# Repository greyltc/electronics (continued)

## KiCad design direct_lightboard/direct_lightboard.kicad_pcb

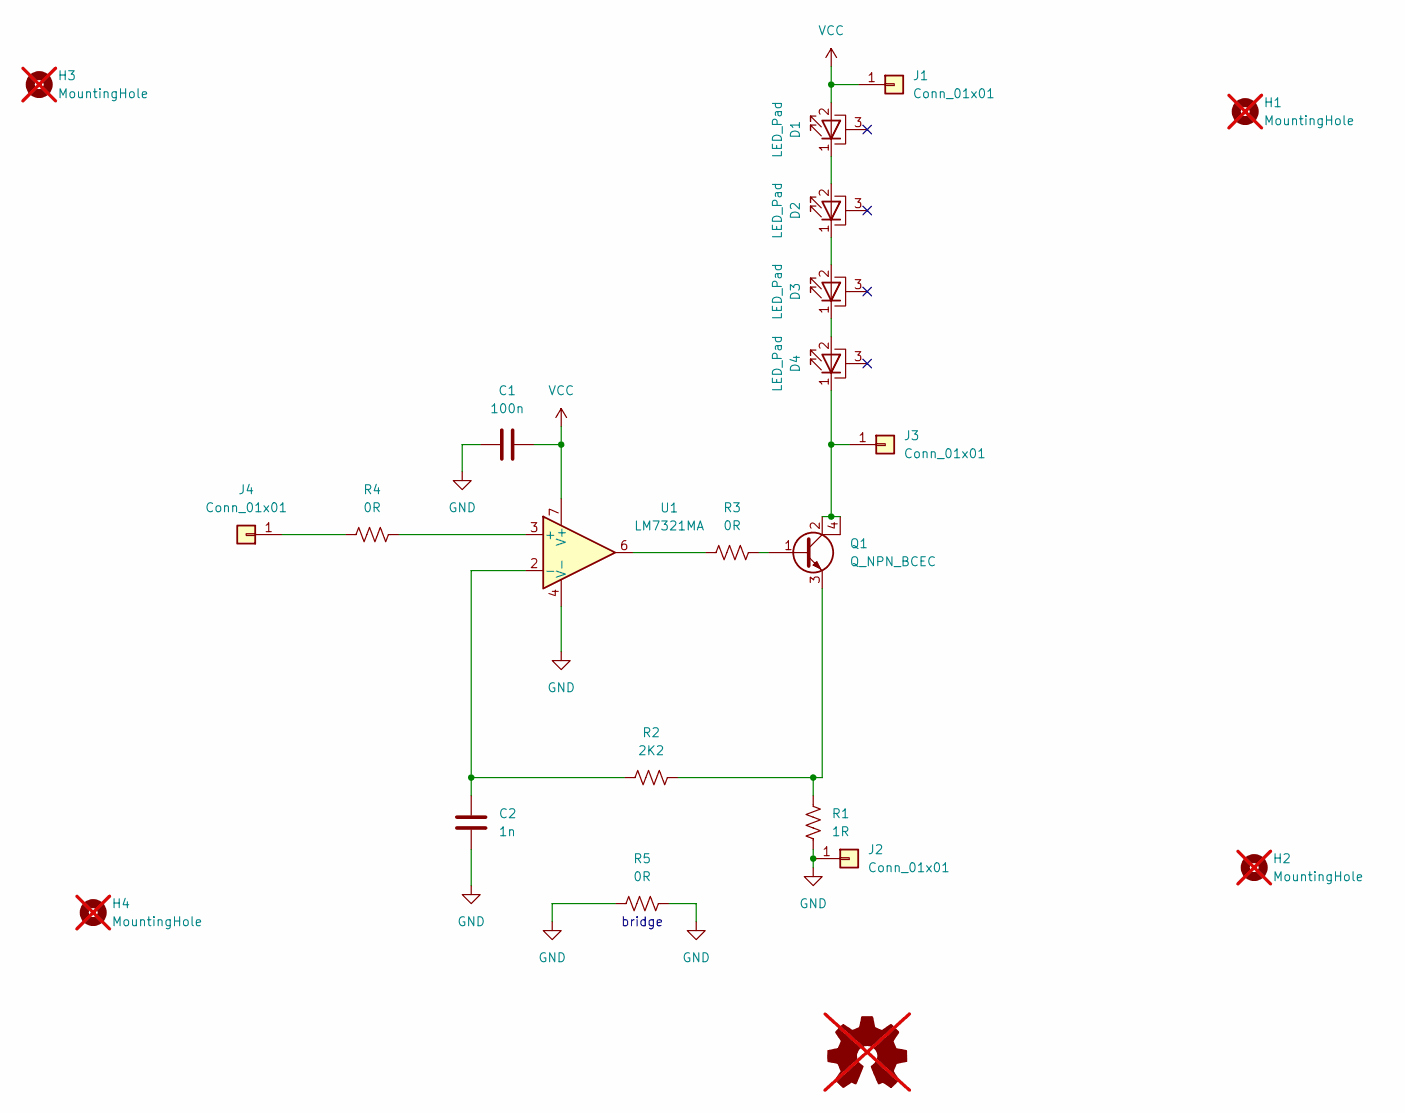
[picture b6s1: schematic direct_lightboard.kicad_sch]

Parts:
C1: 100n; C_0805_2012Metric_Pad1.18x1.45mm_HandSolder; LCSC C77082
C2: 1n; C_0805_2012Metric_Pad1.18x1.45mm_HandSolder; LCSC C46653
D1, D2, D3, D4: LED_Pad; LED_3x3_DIRECT_CU; LCSC C2899049
H1, H2, H3, H4: MountingHole; MountingHole_4mm; not fitted
J1, J2, J3, J4: Conn_01x01; TE_2834006-1_1x01_P4.0mm_Horizontal; LCSC C306142
Q1: Q_NPN_BCEC; SOT-223; LCSC C24098
R1: 1R; R_2512_6332Metric_Pad1.40x3.35mm_HandSolder; LCSC C2941595
R2: 2K2; R_0805_2012Metric_Pad1.20x1.40mm_HandSolder; LCSC C3008897
R3, R4: 0R; R_0805_2012Metric_Pad1.20x1.40mm_HandSolder; LCSC C844192
R5: 0R; R_1206_3216Metric_Pad1.30x1.75mm_HandSolder; LCSC C844862
SYM1: Logo_Open_Hardware_Small; site_small; not fitted
U1: LM7321MA; VSSOP-8_3.0x3.0mm_P0.65mm; LCSC C81665

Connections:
GND: C1.1, C2.1, J2.1, R1.2, R5.1, R5.2, U1.4 (V-)
unnamed: D1.1 (K), D2.2 (A)
unnamed: D2.1 (K), D3.2 (A)
unnamed: D3.1 (K), D4.2 (A)
unnamed: D4.1 (K), J3.1, Q1.2 (C), Q1.4 (C)
unnamed: J4.1, R4.1
unnamed: Q1.1 (B), R3.2
unnamed: Q1.3 (E), R1.1, R2.2
unnamed: R3.1, U1.6
unnamed: R4.2, U1.3 (+)
unnamed: C2.2, R2.1, U1.2 (-)
VCC: C1.2, D1.2 (A), J1.1, U1.7 (V+)

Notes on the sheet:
bridge

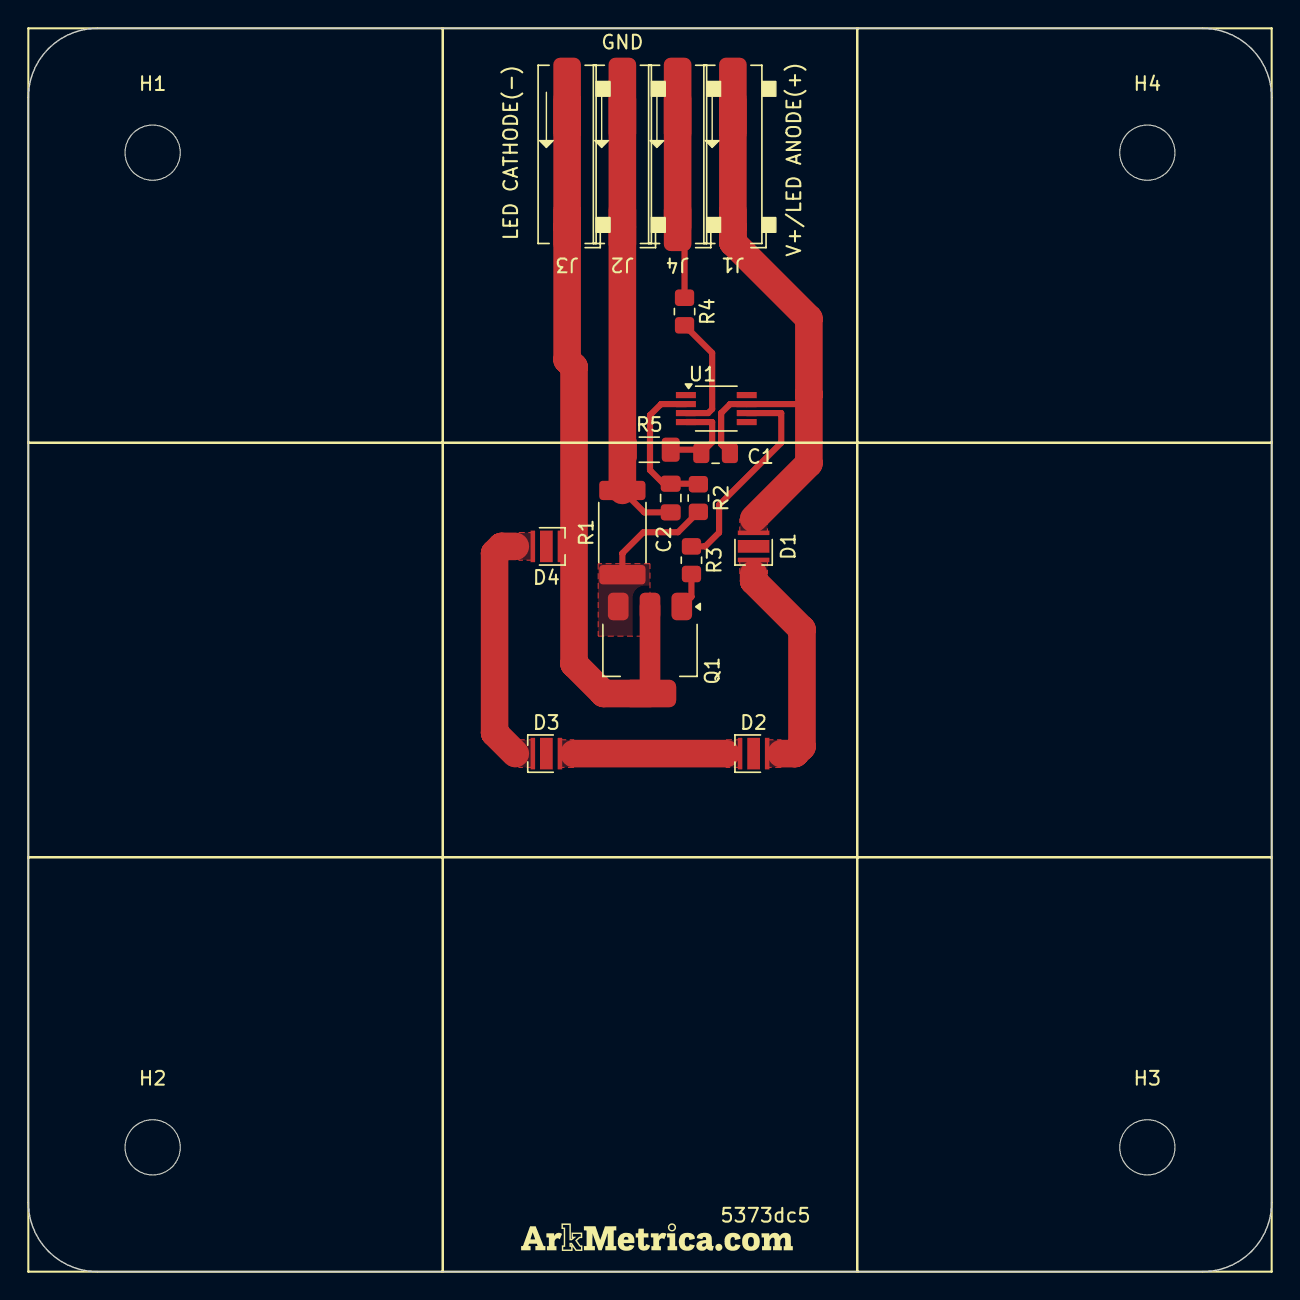
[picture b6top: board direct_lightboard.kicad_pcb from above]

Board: 2 copper layers, 90.0 x 90.0 mm, 22 parts (0 on the bottom side), 12 nets.

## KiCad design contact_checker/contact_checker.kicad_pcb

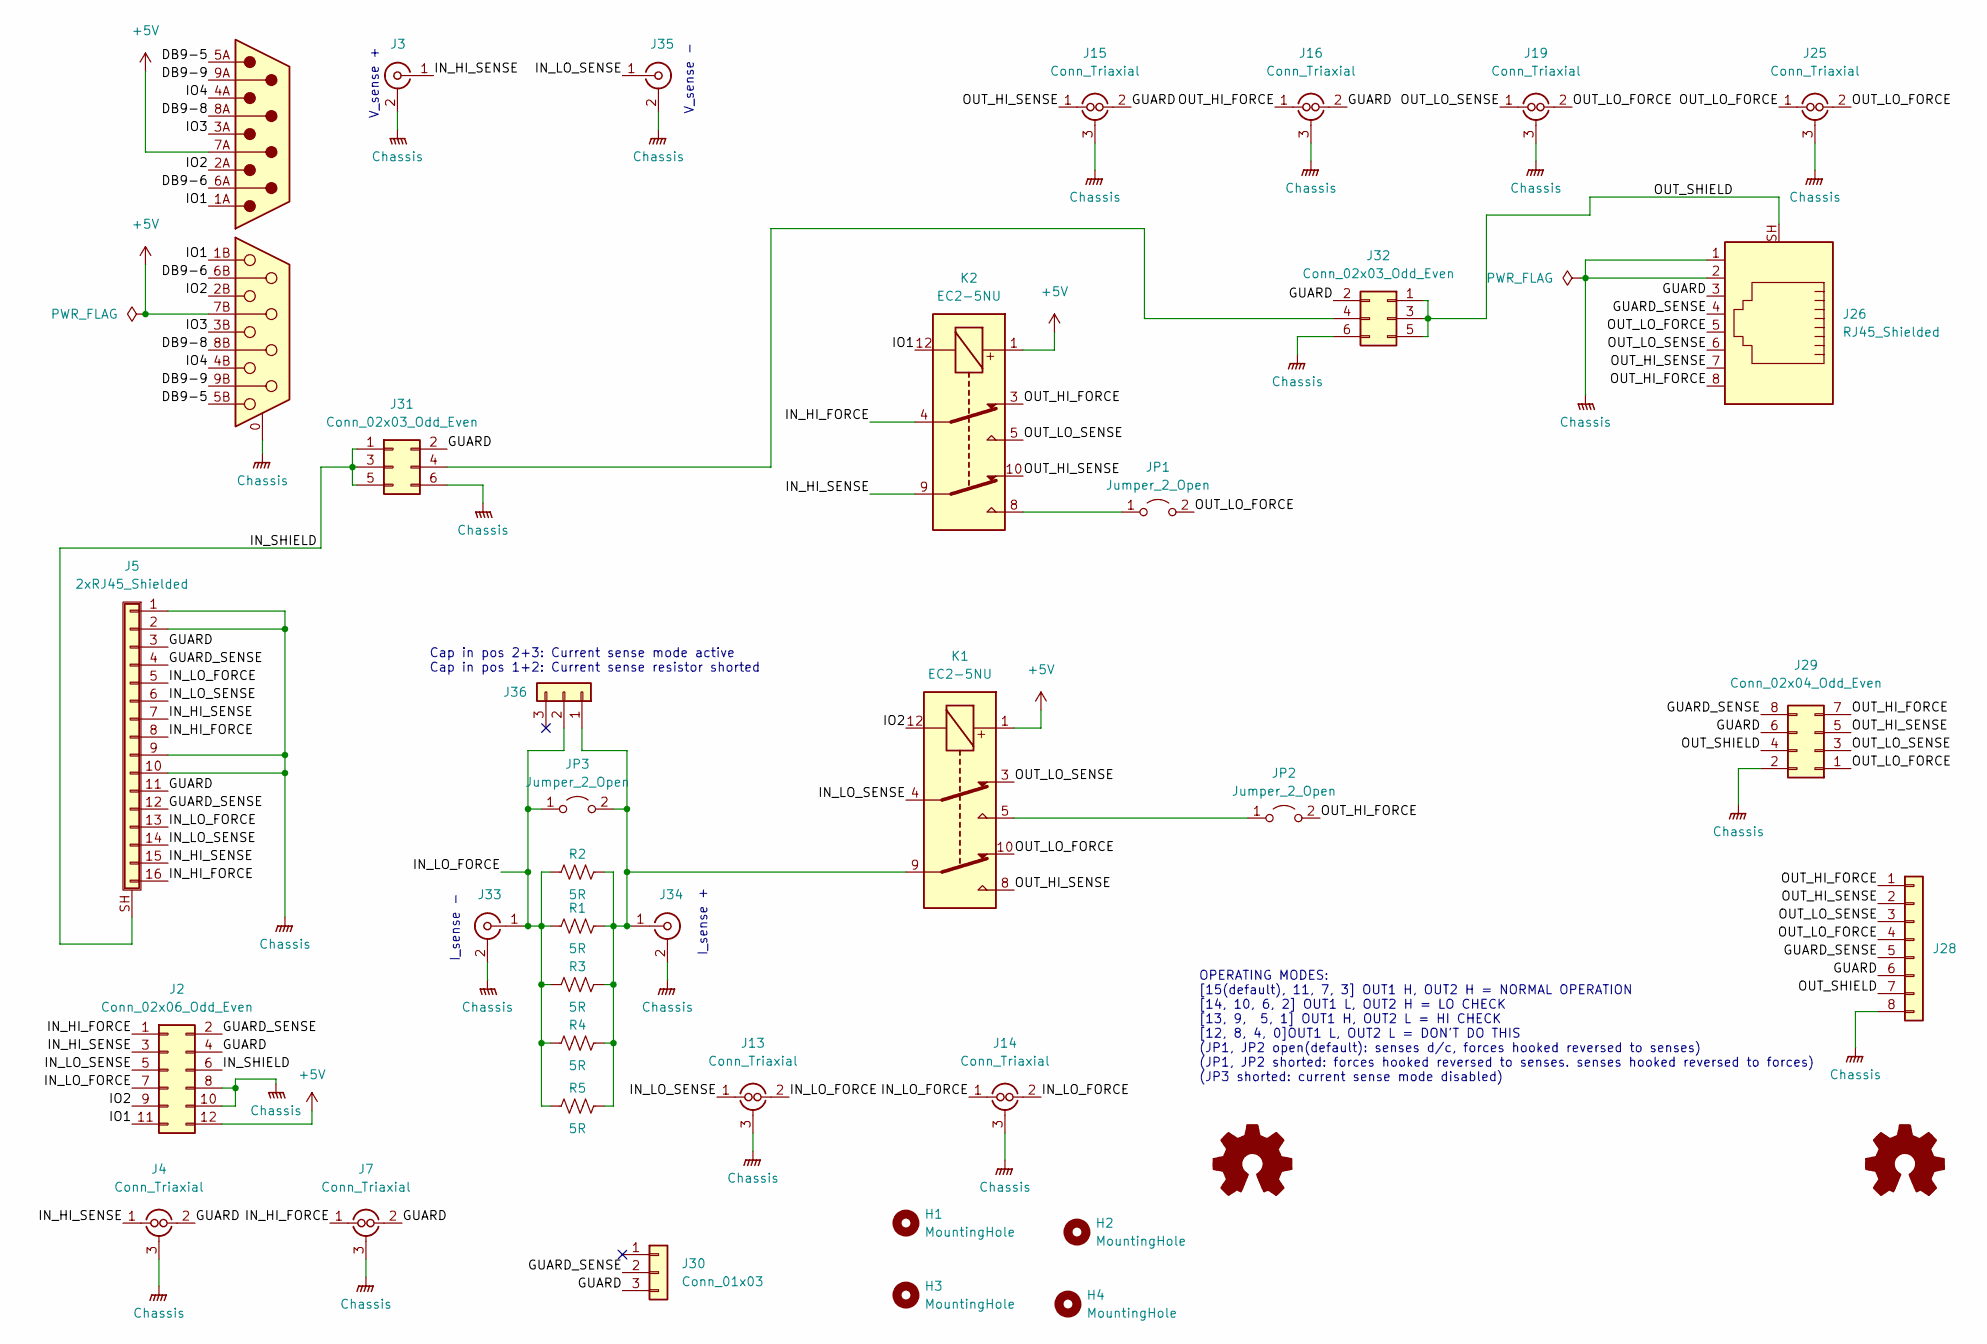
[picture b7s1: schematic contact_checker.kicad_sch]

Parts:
H1, H2, H3, H4: MountingHole; MountingHole_3.2mm_M3_ISO7380
J1: DB9_Male_Female_Stack_MountingHoles; DSUB-9_Male_Female_Vertical_Stack_P2.77x2.84mm_MountingHoles
J2: Conn_02x06_Odd_Even; IDC-Header_2x06_P2.54mm_Horizontal
J3, J33, J34, J35: Conn_Coaxial; U.FL_Molex_MCRF_73412-0110_Vertical
J4, J7, J13, J14, J15, J16, J19, J25: Conn_Triaxial; PinHeader_1x03_P2.54mm_Vertical
J5: 2xRJ45_Shielded; RJ45_WURTH_615016240521
J26: RJ45_Shielded; RJ45_WURTH_61500814221
J28: Conn_01x08; PhoenixContact_MC_1,5_8-GF-3.5_1x08_P3.50mm_Horizontal_Thre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
J29: Conn_02x04_Odd_Even; IDC-Header_2x04_P2.54mm_Horizontal
J30, J36: Conn_01x03; PinHeader_1x03_P2.54mm_Horizontal
J31, J32: Conn_02x03_Odd_Even; PinHeader_2x03_P2.54mm_Vertical
JP1, JP2: Jumper_2_Open; SolderJumper-2_P1.3mm_Open_TrianglePad1.0x1.5mm
JP3: Jumper_2_Open; SolderJumper-2_P1.3mm_Open_RoundedPad1.0x1.5mm
K1, K2: EC2-5NU; Relay_DPDT_Kemet_EC2
LOGO1, LOGO2: Logo_Open_Hardware_Small; logo
R1, R2, R3, R4, R5: 5R; R_2512_6332Metric_Pad1.40x3.35mm_HandSolder

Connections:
+5V: J1.7A, J1.7B, J2.12, K1.1, K2.1
/DB9-5: J1.5A, J1.5B
/DB9-6: J1.6A, J1.6B
/DB9-8: J1.8A, J1.8B
/DB9-9: J1.9A, J1.9B
/GUARD: J2.4, J4.2 (In2), J5.3, J5.11, J7.2 (In2), J15.2 (In2), J16.2 (In2), J26.3, J28.6, J29.6, J30.3, J31.2, J32.2
/GUARD_SENSE: J2.2, J5.4, J5.12, J26.4, J28.5, J29.8, J30.2
/IN_HI_FORCE: J2.1, J5.8, J5.16, J7.1 (In1), K2.4
/IN_HI_SENSE: J2.3, J3.1 (In), J4.1 (In1), J5.7, J5.15, K2.9
/IN_LO_FORCE: J2.7, J5.5, J5.13, J13.2 (In2), J14.1 (In1), J14.2 (In2), J33.1 (In), J36.2, JP3.1 (A), R1.1, R2.1, R3.1, R4.1, R5.1
/IN_LO_SENSE: J2.5, J5.6, J5.14, J13.1 (In1), J35.1 (In), K1.4
/IN_SHIELD: J2.6, J5.SH (Shield), J31.1, J31.3, J31.5
/IO1: J1.1A, J1.1B, J2.11, K2.12
/IO2: J1.2A, J1.2B, J2.9, K1.12
/IO3: J1.3A, J1.3B
/IO4: J1.4A, J1.4B
/OUT_HI_FORCE: J16.1 (In1), J26.8, J28.1, J29.7, JP2.2 (B), K2.3
/OUT_HI_SENSE: J15.1 (In1), J26.7, J28.2, J29.5, K1.8, K2.10
/OUT_LO_FORCE: J19.2 (In2), J25.1 (In1), J25.2 (In2), J26.5, J28.4, J29.1, JP1.2 (B), K1.10
/OUT_LO_SENSE: J19.1 (In1), J26.6, J28.3, J29.3, K1.3, K2.5
/OUT_SHIELD: J26.SH, J28.7, J29.4, J32.1, J32.3, J32.5
GNDPWR: J1.0 (PAD), J2.8, J2.10, J3.2 (Ext), J4.3 (Ext), J5.1, J5.2, J5.9, J5.10, J7.3 (Ext), J13.3 (Ext), J14.3 (Ext), J15.3 (Ext), J16.3 (Ext), J19.3 (Ext), J25.3 (Ext), J26.1, J26.2, J28.8, J29.2, J31.6, J32.6, J33.2 (Ext), J34.2 (Ext), J35.2 (Ext)
unnamed: J31.4, J32.4
unnamed: J34.1 (In), J36.1, JP3.2 (B), K1.9, R1.2, R2.2, R3.2, R4.2, R5.2
unnamed: JP1.1 (A), K2.8
unnamed: JP2.1 (A), K1.5

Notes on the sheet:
V_sense +
I_sense -
I_sense +
V_sense -
OPERATING MODES: [15(default), 11, 7, 3] OUT1 H, OUT2 H = NORMAL OPERATION [14, 10, 6, 2] OUT1 L, OUT2 H = LO CHECK [13, 9, 5, 1] OUT1 H, OUT2 L = HI CHECK [12, 8, 4, 0]OUT1 L, OUT2 L = DON'T DO THIS (JP1, JP2 open(default): senses d/c, forces hooked reversed to senses) (JP1, JP2 shorted: forces ho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
Cap in pos 2+3: Current sense mode active Cap in pos 1+2: Current sense resistor shorted

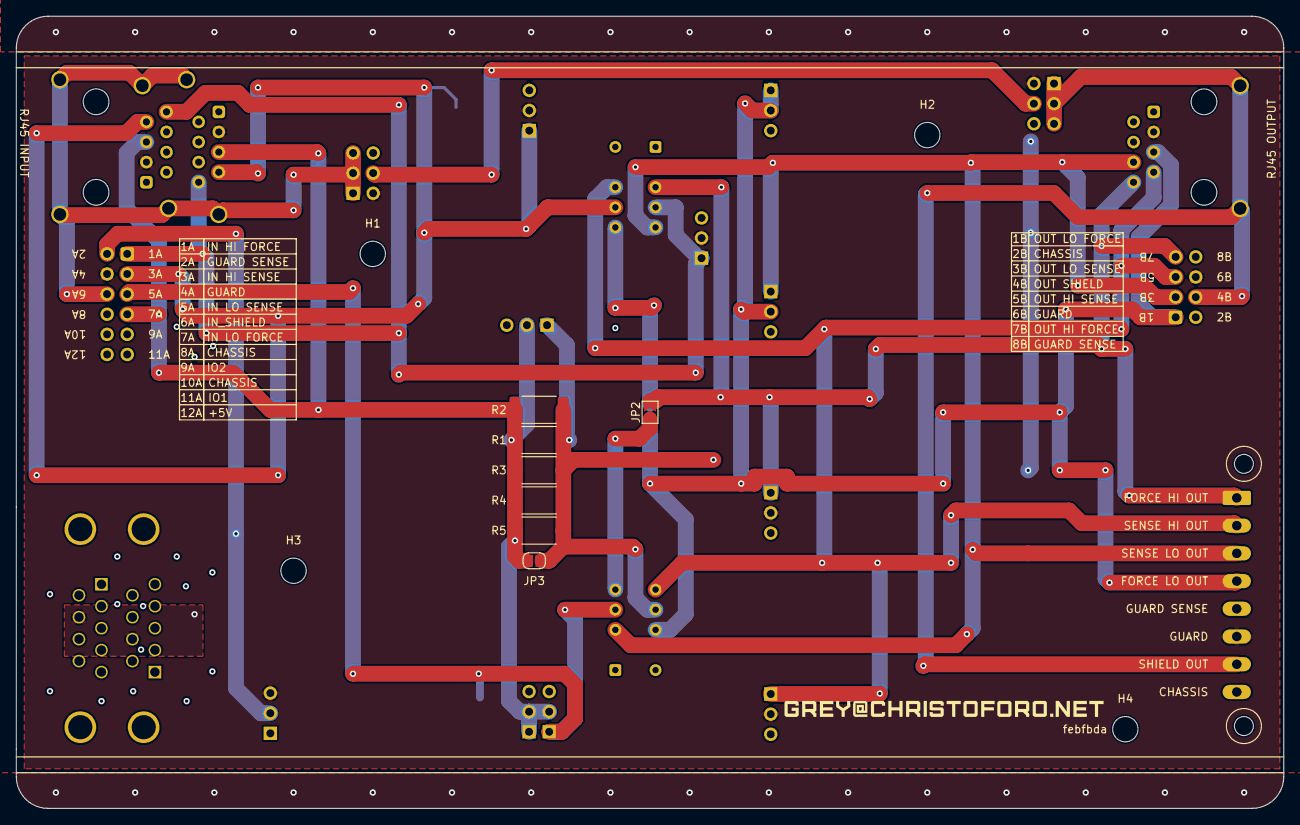
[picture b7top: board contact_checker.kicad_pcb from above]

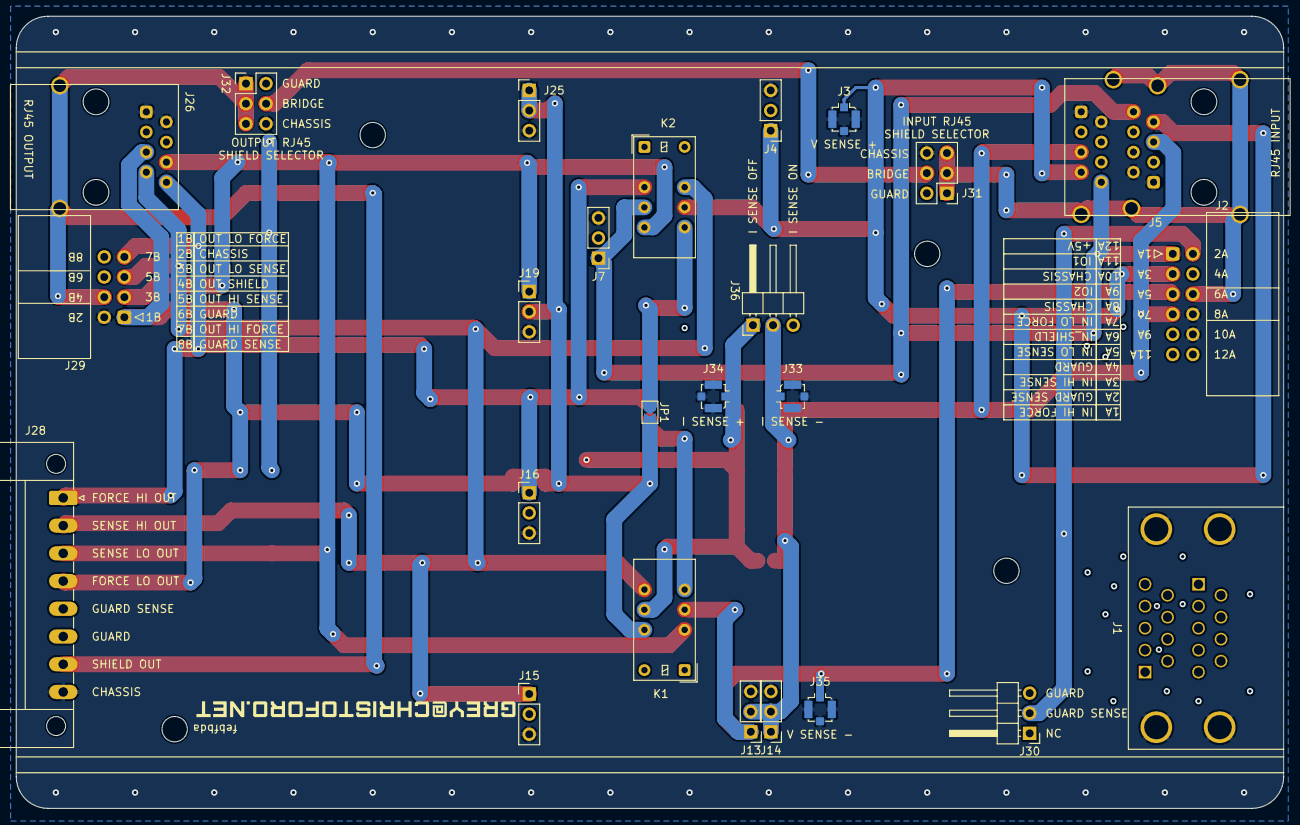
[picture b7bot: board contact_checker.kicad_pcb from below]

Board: 4 copper layers, 160.0 x 100.0 mm, 38 parts (26 on the bottom side), 26 nets.

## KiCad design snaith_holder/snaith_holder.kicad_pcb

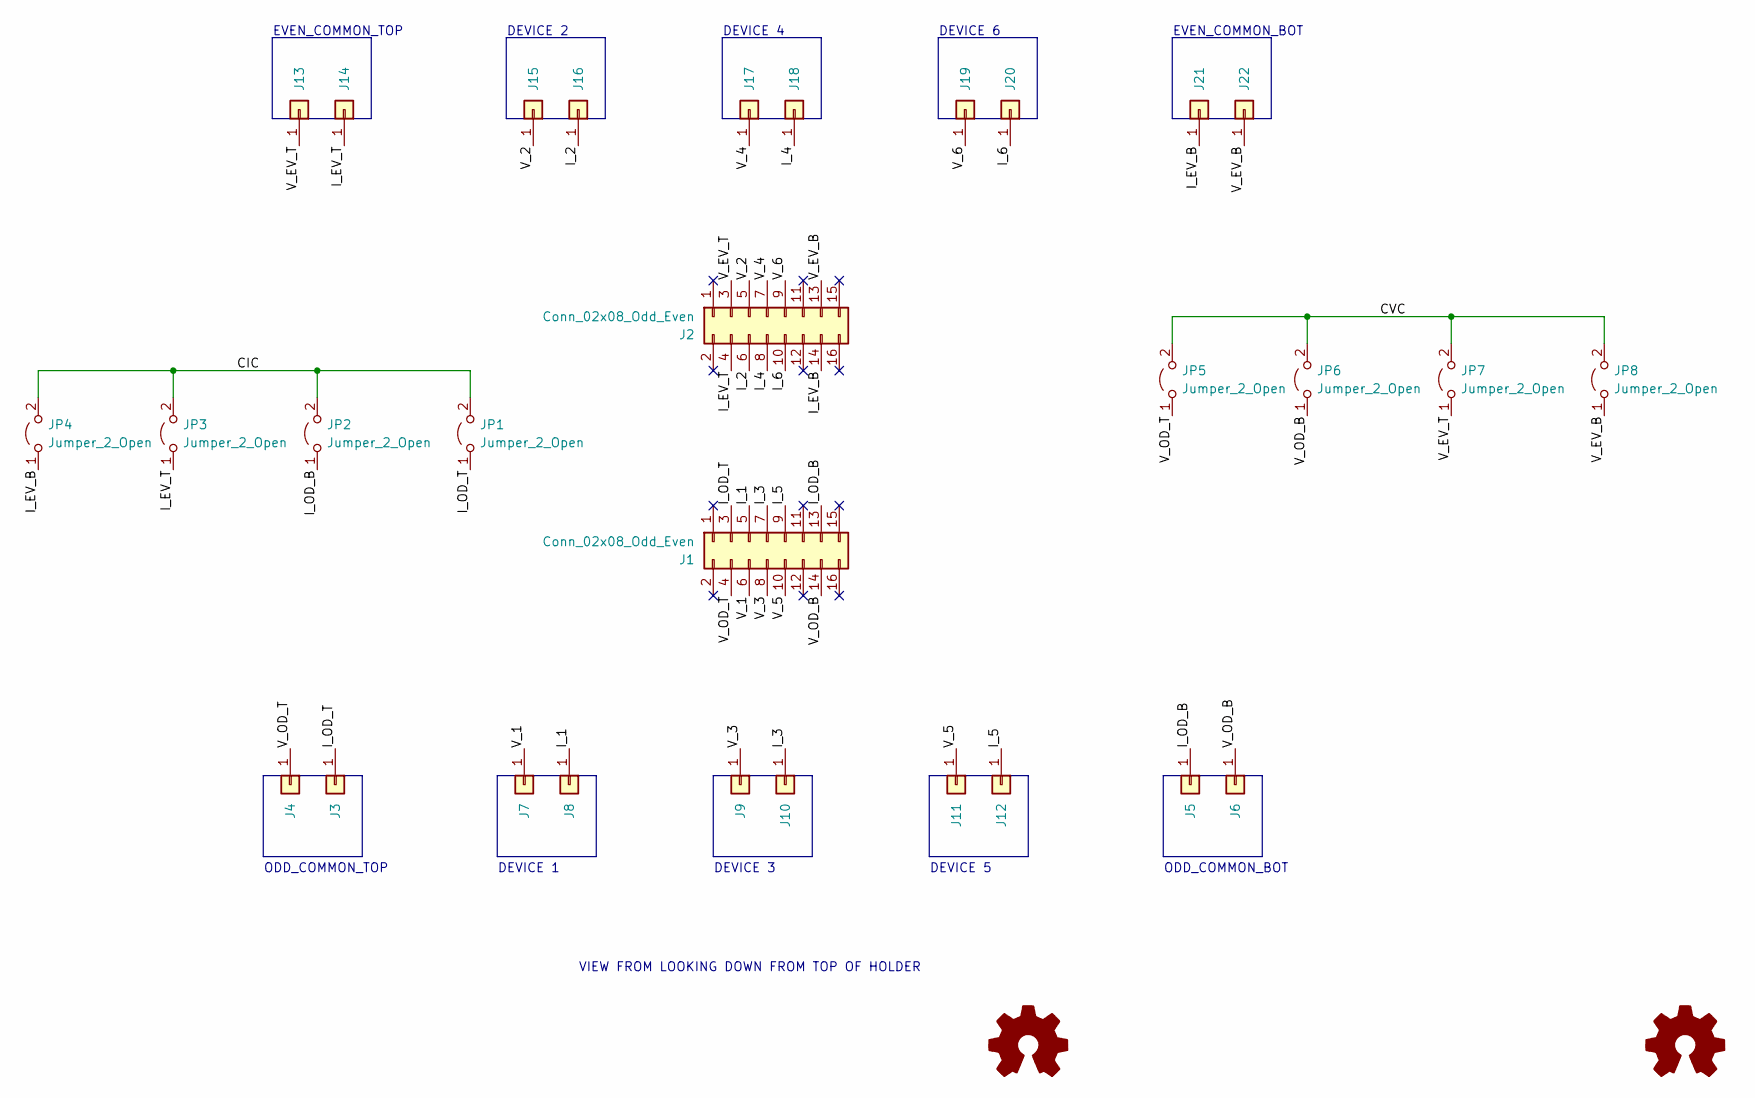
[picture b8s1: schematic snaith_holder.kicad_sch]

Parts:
J1: Conn_02x08_Odd_Even; HIF3FC-16PA-2.54DSA(71); partno_receptical HIF3FB-16DA-2.54DSA(71)
J2: Conn_02x08_Odd_Even; HIF3FC-16PA-2.54DSA(71); partno_header HIF3FC -16PA-2.54DSA(71)
J3, J4, J5, J6, J7, J8, J9, J10, J11, J12, J13, J14, J15, J16, J17, J18, J19, J20, J21, J22: Conn_01x01; S25-022+P25-4023_OFF
JP1, JP2, JP3, JP4, JP5, JP6, JP7, JP8: Jumper_2_Open; SolderJumper-2_P1.3mm_Open_TrianglePad1.0x1.5mm
SYM1, SYM2: Logo_Open_Hardware_Small; logo_small

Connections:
/CIC: JP1.2 (B), JP2.2 (B), JP3.2 (B), JP4.2 (B)
/CVC: JP5.2 (B), JP6.2 (B), JP7.2 (B), JP8.2 (B)
/I_1: J1.5, J8.1
/I_2: J2.6, J16.1
/I_3: J1.7, J10.1
/I_4: J2.8, J18.1
/I_5: J1.9, J12.1
/I_6: J2.10, J20.1
/I_EV_B: J2.14, J21.1, JP4.1 (A)
/I_EV_T: J2.4, J14.1, JP3.1 (A)
/I_OD_B: J1.13, J5.1, JP2.1 (A)
/I_OD_T: J1.3, J3.1, JP1.1 (A)
/V_1: J1.6, J7.1
/V_2: J2.5, J15.1
/V_3: J1.8, J9.1
/V_4: J2.7, J17.1
/V_5: J1.10, J11.1
/V_6: J2.9, J19.1
/V_EV_B: J2.13, J22.1, JP8.1 (A)
/V_EV_T: J2.3, J13.1, JP7.1 (A)
/V_OD_B: J1.14, J6.1, JP6.1 (A)
/V_OD_T: J1.4, J4.1, JP5.1 (A)

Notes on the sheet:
ODD_COMMON_TOP
EVEN_COMMON_BOT
DEVICE 6
DEVICE 4
ODD_COMMON_BOT
VIEW FROM LOOKING DOWN FROM TOP OF HOLDER
DEVICE 3
DEVICE 5
DEVICE 2
EVEN_COMMON_TOP
DEVICE 1

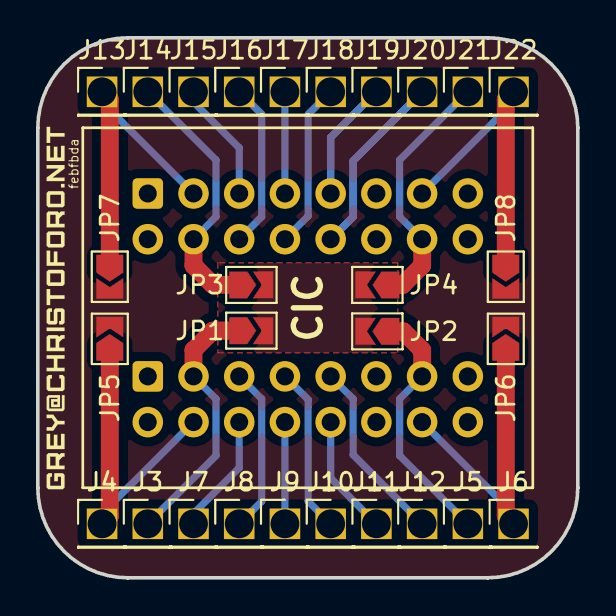
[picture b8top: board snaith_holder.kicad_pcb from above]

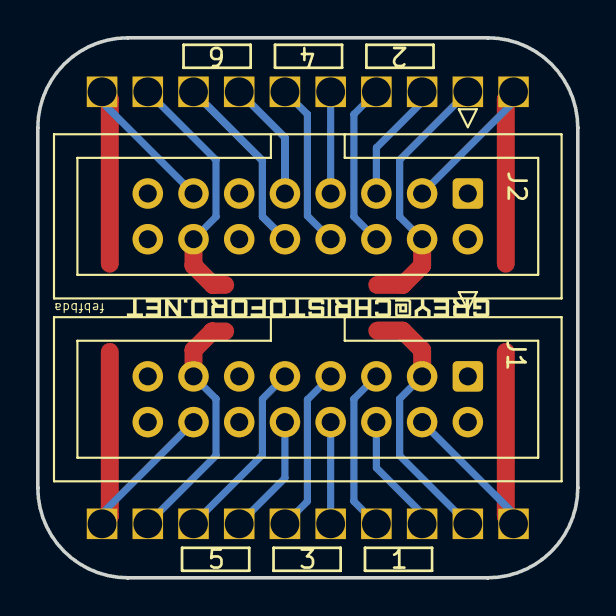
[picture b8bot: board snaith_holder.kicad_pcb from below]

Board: 2 copper layers, 30.0 x 30.0 mm, 32 parts (3 on the bottom side), 22 nets.

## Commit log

2019-08-12 add gitignore
2019-08-12 gnore
2019-08-20 matrix switch design done
2019-08-22 wip on matrix switch card edge adapter board
2019-11-11 matrix switch wip
2019-11-13 add lim chamber plan
2019-11-14 move otter electronics here
2019-11-14 purge output files
2019-11-14 reduce otter pin drill hole diameter
2019-11-14 update silk
2019-11-22 lim crossbar pcb done
2019-11-22 add lim crossbar
2019-11-25 update spring pin hole size and improve crossbar routing
2019-12-02 crossbar work
2019-12-07 wip on crossbars
2019-12-31 otter crossbars shortened
2020-01-09 pre basebord freeroute
2020-01-10 lim baseboard done
2020-01-15 otter crossbar modified
2020-01-16 add features to oxford adapter
2020-01-22 start baseboard
2020-01-23 baseboard routed
2020-01-27 fix baseboard connector position
2020-01-29 enbiggen pcb dowel holes
2020-02-02 design otter photodiode board
2020-02-02 add pad vias
2020-02-02 move pdb pad vias out
2020-02-03 update pdb silk and add missing letter to otter baseboard
2020-03-11 fix lim baseboard bug
2020-09-10 add some LED mockup renders
2021-02-04 take snapshot
2021-02-04 add spicy
2021-02-07 add simulation
2021-02-10 add initial badger design
2021-02-10 check over and minor updates for old mux design
2021-02-11 badger upgrades
2021-03-10 crossbar redesign to get linear trace highway
2021-03-14 redesign adapter mount
2021-04-04 wip on 4x1 crossbar
2021-04-04 remove step
2021-04-06 top pcb doneish
2021-04-07 aux boards done
2021-04-08 small changes for mfg
2021-04-10 wip on otter 50x50
2021-04-10 rm fake footprint
2021-04-15 new otter and badger boards done
2021-04-15 fab update
2021-06-04 update adapter boards for pressfit
2021-07-31 add portenta, start work on arkplat
2021-08-05 wip on poe
2021-10-06 update led mockup
2021-11-16 some mods
2021-11-16 add stranks mockup
2022-04-10 squirrel wip
2022-04-23 wip on sq
2022-04-23 wip on squ
2022-04-25 wip on sq pcb
2022-05-06 wip on sqpcb
2022-06-04 fix up connectors
2022-06-04 finish fixing footprints
2022-06-07 smaller pt pcb
2022-07-04 sqpcbs layed out
2022-07-04 silk
2022-07-04 add dummy copper
2022-08-09 wip on contact checker
2022-08-09 file sync
2022-08-12 contact checker lyout done
2022-08-12 exported
2022-08-21 wip on arkplat
2022-08-23 contact checker updates
2022-08-24 rj45 adapter done. contact checker reworked
2022-08-25 update rj45 adapter and contact checker to v2
2022-08-26 improve shield selection
2022-08-26 make some fab files
2022-09-04 new chassis sidebars and input connectors
2022-09-06 switch to stacked DB9 connector to save edge space
2022-09-07 rev3 on contact checker boards
2022-09-09 add silk notes to contact checker
2022-09-09 cc rev3 panels
2023-05-18 wip on switches
2023-06-09 spruce up the switches
2023-06-15 switches pcb complete
2023-06-23 wip on hoye holer pcb
2023-07-01 wip on hoye
2023-07-13 new holder pcbs
2023-07-14 plotted
2023-08-21 change some logos
2023-08-21 make legacy substrate adapter pcbs
2023-08-22 upgrade contact checker with sense circuitry
2023-08-23 make rj45 breakout
2023-08-23 add some missing copper
2023-08-23 add some missing silkscreen
2023-09-16 move some silk
2023-09-17 fix missing trace
2023-12-07 new lightboard design
2023-12-15 make rabbit baseboard
2023-12-19 contact checker fixups
2023-12-19 fix up in&out cc panels
2024-01-17 make two sided
2024-01-17 change 1234 to abcd
2024-02-19 add battery clip
2024-02-19 rm fp-info-cache
2024-02-25 move connector to edge
2024-02-25 fix up rj45 pad numbering
2024-02-25 switch contact checker's rj45 part
2024-02-25 remove banana cons from contact checker
2024-02-25 shrink steps, add double rj45 to cc
2024-02-26 add plate holes to cc and update holder with shorts
2024-03-25 wip on direct thermal
2024-03-26 fix connector spacing
2024-04-09 move relays to the other side of the board
2024-05-18 wip on lb
2024-12-31 add fourch board
2025-06-12 add new hoye holder board
2025-09-28 rev up fourch lights, add distroboard
2025-09-28 fix up lightboard
2025-09-29 minor touchups
2025-09-29 fillet corners
2025-09-29 switch opamps to dual flavors, build in on-board TEC current control
2025-09-29 add single board distro
2025-09-29 fix up bom
2025-09-29 after plotting
2025-09-30 update bom
2025-09-30 rename bomfile
2025-12-29 rev up light
2025-12-31 wip on platform board
2025-12-31 remove copy
